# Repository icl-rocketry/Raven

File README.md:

# Project RAVEN

Solid-state particle detector for a rocket payload. Detects cosmic radiation
throughout flight and logs each hit with altitude, to build up counting
statistics post-flight.

Built in KiCad. Mixed-signal board: the detector board reads two independent
silicon-diode detector channels and logs events. 

## How it works 

A cosmic particle hits a reverse-biased photodiode and dumps a few femtocoulombs
of charge. A charge-sensitive amplifier turns that into a ~7 mV pulse, a
comparator checks it against a tunable threshold and the output signal is processed
by a seperate Pickle Rick board. Two diodes on two independent
channels double the sensitive area without doubling the noise.

## Repository layout

The KiCad project has five schematic sheets:
Using the ICLR Board Template

| Sheet | Contents |
|-------|----------|
| Root | status LEDs, connectors, test points |
| Power Board | Three isolated rails off a ~7.4V battery: +25V bias, +5V analogue, +3.3V digital |
| Detector Board | The signal chain: diodes, charge amps, comparators (2 channels) |

## specs

- **Enclosure:** Circa 90 x 90 x 100 mm (TBD), light-tight detector housing
- **Power:** ~1.5 W from a ~7.4V battery (cell TBC)
- **Detector:** 2x BPW34 photodiodes, biased at +50V
- **Front-end:** ADA4817-1 charge amp, TLV3201 comparator, per channel
- **MCU:** ESP32-S3

## Status

Work in progress. Schematic of the detector front-end is nearly
complete; layout, bring-up, and firmware still to come.

**Outstanding before layout:**
- Confirm comparator edge polarity on the bench (rising vs falling) before
  writing interrupt firmware
- Clear all ERC

## Firmware

Firmware is set up for PlatformIO. Clone the repo and open in PlatformIO to
build and flash.

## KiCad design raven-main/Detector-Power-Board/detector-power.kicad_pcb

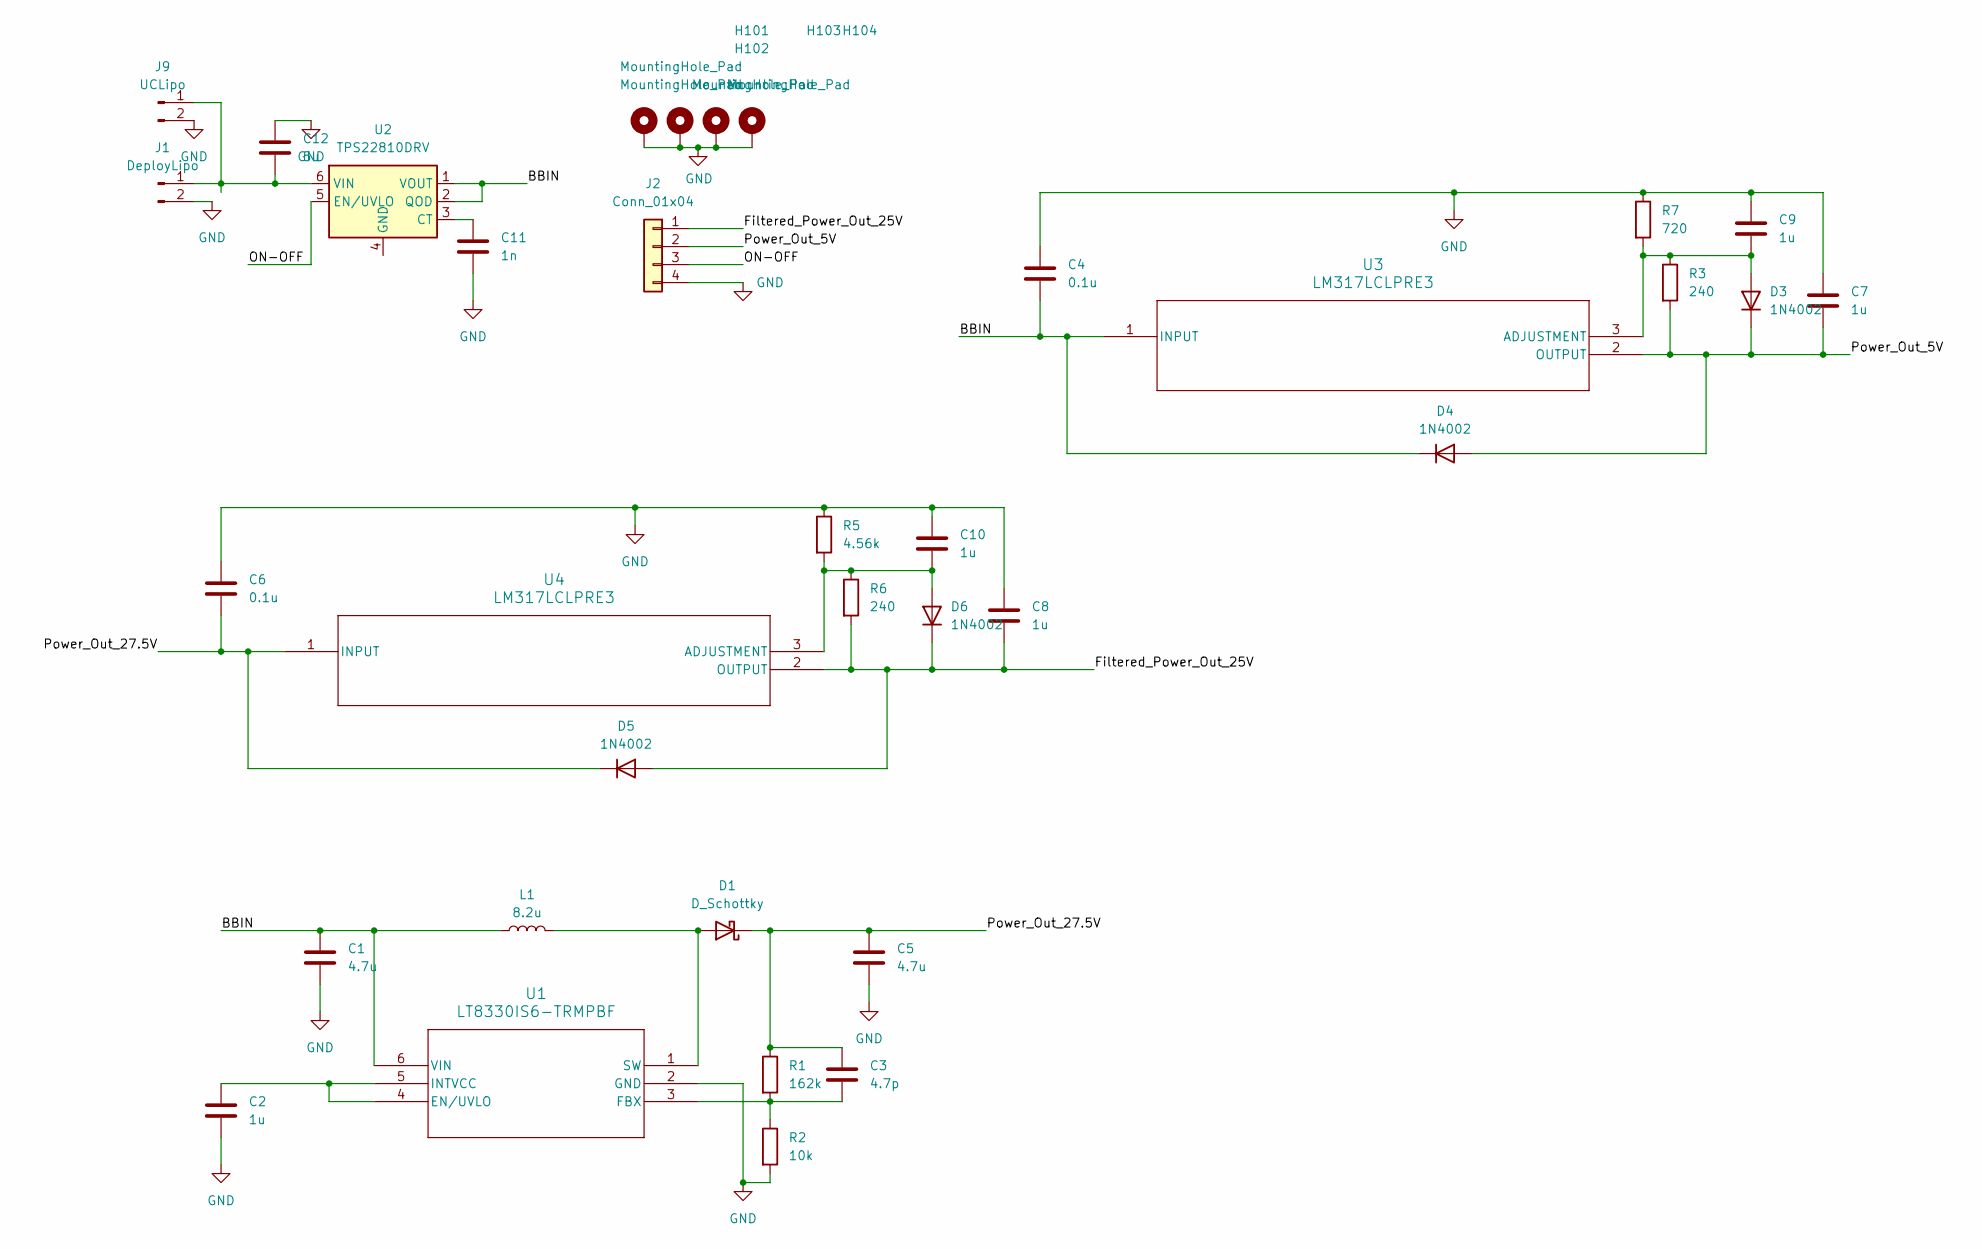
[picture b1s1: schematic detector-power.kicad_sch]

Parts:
C1, C5: 4.7u; C_0805_2012Metric
C2, C7, C8, C9, C10: 1u; C_0805_2012Metric
C3: 4.7p; C_0805_2012Metric
C4, C6: 0.1u; C_0805_2012Metric
C11: 1n; C_0805_2012Metric
C12: 5u; C_0805_2012Metric
D1: D_Schottky; SOD323F_NEX
D3, D4, D5, D6: 1N4002; D_DO-41_SOD81_P10.16mm_Horizontal
H101, H102, H103, H104: MountingHole_Pad; MountingHole_3.2mm_M3_DIN965_Pad
J1: DeployLipo; TerminalBlock_Phoenix_MKDS-3-2-5.08_1x02_P5.08mm_Horizontal
J2: Conn_01x04; PinHeader_1x04_P2.54mm_Vertical
J9: UCLipo; JST_PH_B2B-PH-K_1x02_P2.00mm_Vertical
L1: 8.2u; IND_8R0NC_SUM
R1: 162k; R_0402_1005Metric
R2: 10k; R_0402_1005Metric
R3, R6: 240; R_0402_1005Metric
R5: 4.56k; R_0402_1005Metric
R7: 720; R_0402_1005Metric
U1: LT8330IS6-TRMPBF; IC6_LT8330IS6-TRMPBF_ADI
U2: TPS22810DRV; WSON-6-1EP_2x2mm_P0.65mm_EP1x1.6mm
U3, U4: LM317LCLPRE3; TD03B_TEX

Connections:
/BBIN: C1.1, C4.2, D4.1 (K), L1.1, U1.6 (VIN), U2.1 (VOUT), U2.2 (QOD), U3.1 (INPUT)
/Filtered_Power_Out_25V: C8.2, D5.2 (A), D6.1 (K), J2.1, R6.2, U4.2 (OUTPUT)
/ON-OFF: J2.3, U2.5 (EN/UVLO)
/Power_Out_5V: C7.2, D3.1 (K), D4.2 (A), J2.2, R3.2, U3.2 (OUTPUT)
/Power_Out_27.5V: C3.1, C5.1, C6.2, D1.1 (K), D5.1 (K), R1.1, U4.1 (INPUT)
GND: C1.2, C2.2, C4.1, C5.2, C6.1, C7.1, C8.1, C9.1, C10.1, C11.2, C12.2, H101.1 (1_1), H102.1 (1_1), H103.1 (1_1), H104.1 (1_1), J1.2, J2.4, J9.2, R2.2, R5.1, R7.1, U1.2 (GND)
unnamed: D1.2 (A), L1.2, U1.1 (SW)
unnamed: C9.2, D3.2 (A), R3.1, R7.2, U3.3 (ADJUSTMENT)
unnamed: C10.2, D6.2 (A), R5.2, R6.1, U4.3 (ADJUSTMENT)
unnamed: C12.1, J1.1, J9.1, U2.6 (VIN)
unnamed: C2.1, U1.4 (EN/UVLO), U1.5 (INTVCC)
unnamed: C3.2, R1.2, R2.1, U1.3 (FBX)
unnamed: C11.1, U2.3 (CT)
unnamed: U2.4 (GND), U2.7 (GND)

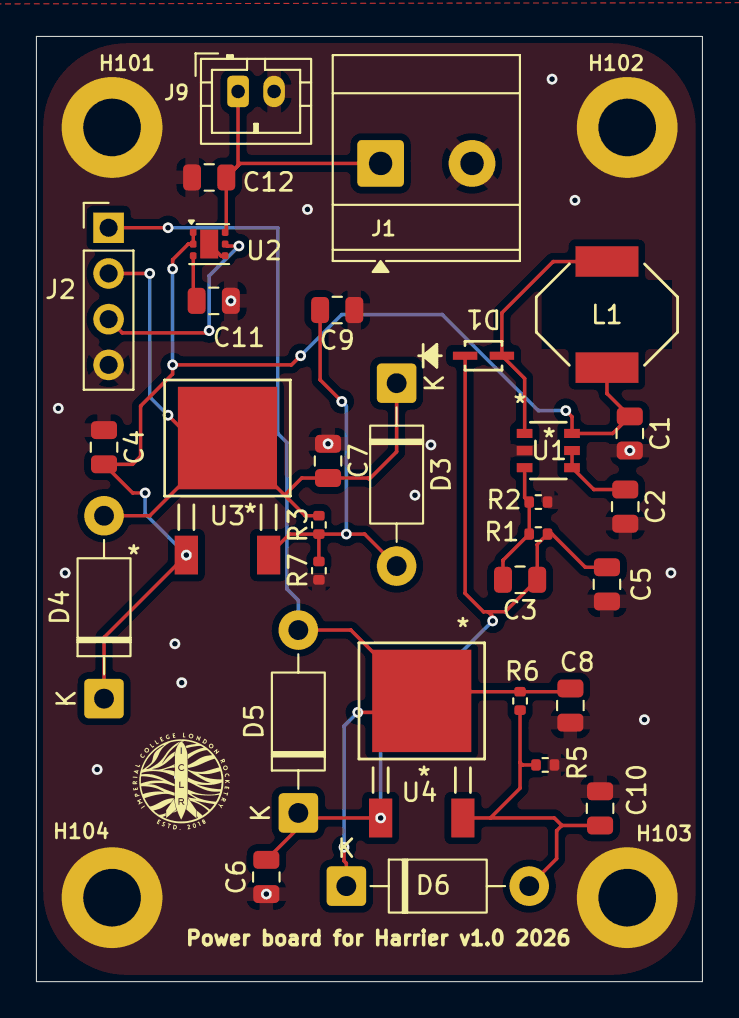
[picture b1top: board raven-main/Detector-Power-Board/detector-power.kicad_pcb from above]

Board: 2 copper layers, 37.0 x 52.5 mm, 35 parts (0 on the bottom side), 14 nets.

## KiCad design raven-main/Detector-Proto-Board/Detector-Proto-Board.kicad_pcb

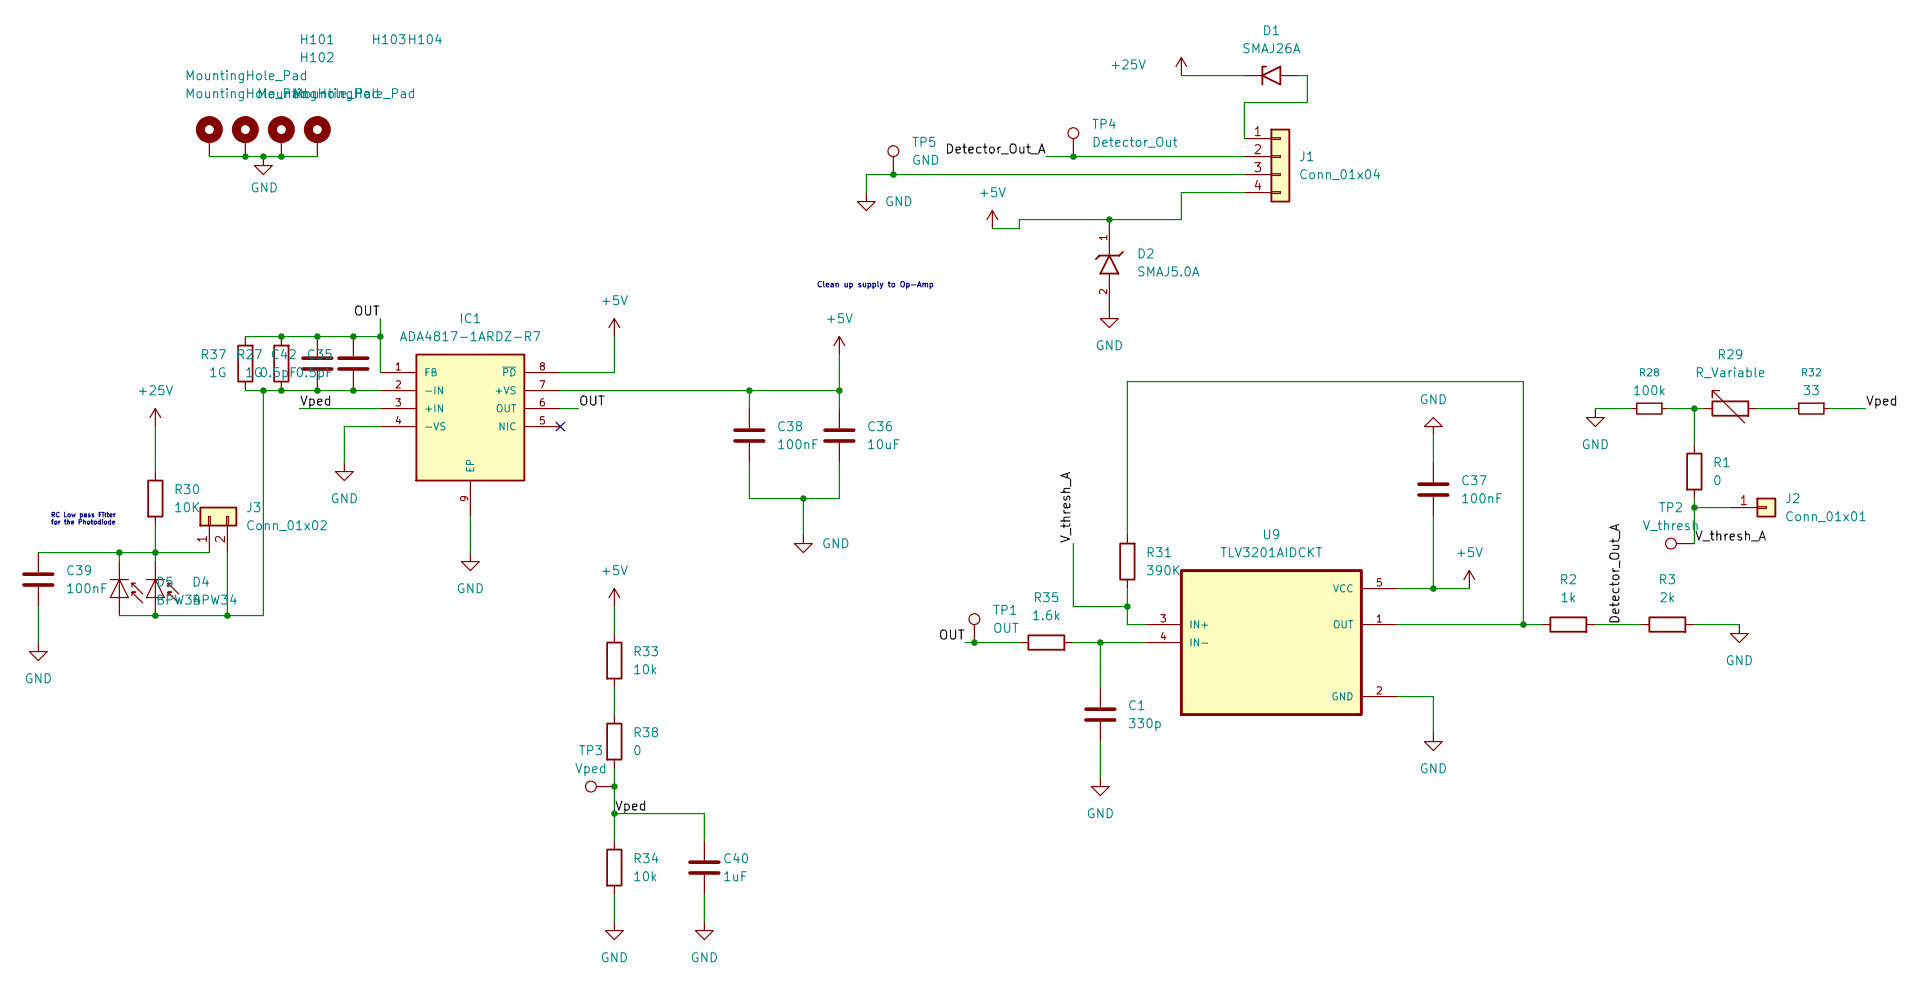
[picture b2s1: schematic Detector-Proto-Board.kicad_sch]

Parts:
C1: 330p; C_0402_1005Metric
C35, C42: 0.5pF; C_0402_1005Metric
C36: 10uF; C_0402_1005Metric
C37, C38, C39: 100nF; C_0402_1005Metric
C40: 1uF; C_0402_1005Metric
D1: SMAJ26A; D_SMA
D2: SMAJ5.0A; D_SMA; MOUSER_PART_NUMBER 576-SMAJ5.0A
D4, D5: BPW34; Osram_DIL2_4.3x4.65mm_P5.08mm
H101, H102, H103, H104: MountingHole_Pad; MountingHole_3.2mm_M3_DIN965_Pad
IC1: ADA4817-1ARDZ-R7; SOIC127P600X175-9N; Mouser_Part_Number 584-ADA4817-1ARDZ-R7
J1: Conn_01x04; PinHeader_1x04_P2.54mm_Vertical
J2: Conn_01x01; PinHeader_1x01_P2.54mm_Vertical
J3: Conn_01x02; PinHeader_1x02_P2.54mm_Vertical
R1, R38: 0; R_0402_1005Metric
R2: 1k; R_0402_1005Metric
R3: 2k; R_0402_1005Metric
R27, R37: 1G; R_0402_1005Metric
R28: 100k; R_0402_1005Metric
R29: R_Variable; SOT_502E
R30: 10K; R_0402_1005Metric
R31: 390K; R_0402_1005Metric
R32: 33; R_0402_1005Metric
R33, R34: 10k; R_0402_1005Metric
R35: 1.6k; R_0402_1005Metric
TP1: OUT; TestPoint_Pad_D2.5mm
TP2: V_thresh; TestPoint_Pad_D2.5mm
TP3: Vped; TestPoint_Pad_D2.5mm
TP4: Detector_Out; TestPoint_Pad_D2.5mm
TP5: GND; TestPoint_Pad_D2.5mm
U9: TLV3201AIDCKT; SOT65P210X110-5N

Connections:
+5V: C36.1, C37.2, C38.2, D2.1, IC1.7 (+VS), IC1.8 (~PD), J1.4, R33.1, U9.5 (VCC)
+25V: D1.1 (A1), R30.1
/Detector_Out_A: J1.2, R2.2, R3.1, TP4.1 (1_1)
/OUT: C35.2, C42.2, IC1.1 (FB), IC1.6 (OUT), R27.2, R35.1, R37.2, TP1.1 (1_1)
/V_thresh_A: J2.1 (Pin_1_1), R1.2, R31.1, TP2.1 (1_1), U9.3 (IN+)
/Vped: C40.1, IC1.3 (+IN), R32.1, R34.1, R38.2, TP3.1 (1_1)
GND: C1.2, C36.2, C37.1, C38.1, C39.2, C40.2, D2.2, H101.1 (1_1), H102.1 (1_1), H103.1 (1_1), H104.1 (1_1), IC1.4 (-VS), IC1.9 (EP), J1.3, R3.2, R28.2, R34.2, TP5.1 (1_1), U9.2 (GND)
unnamed: D1.2 (A2), J1.1
unnamed: C35.1, C42.1, D4.2 (A), D5.2 (A), IC1.2 (-IN), J3.2, R27.1, R37.1
unnamed: C39.1, D4.1 (K), D5.1 (K), J3.1, R30.2
unnamed: R1.1, R28.1, R29.1
unnamed: R29.2, R32.2
unnamed: R33.2, R38.1
unnamed: C1.1, R35.2, U9.4 (IN-)
unnamed: R2.1, R31.2, U9.1 (OUT)

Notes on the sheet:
Clean up supply to Op-Amp
RC Low pass Filter for the Photodiode

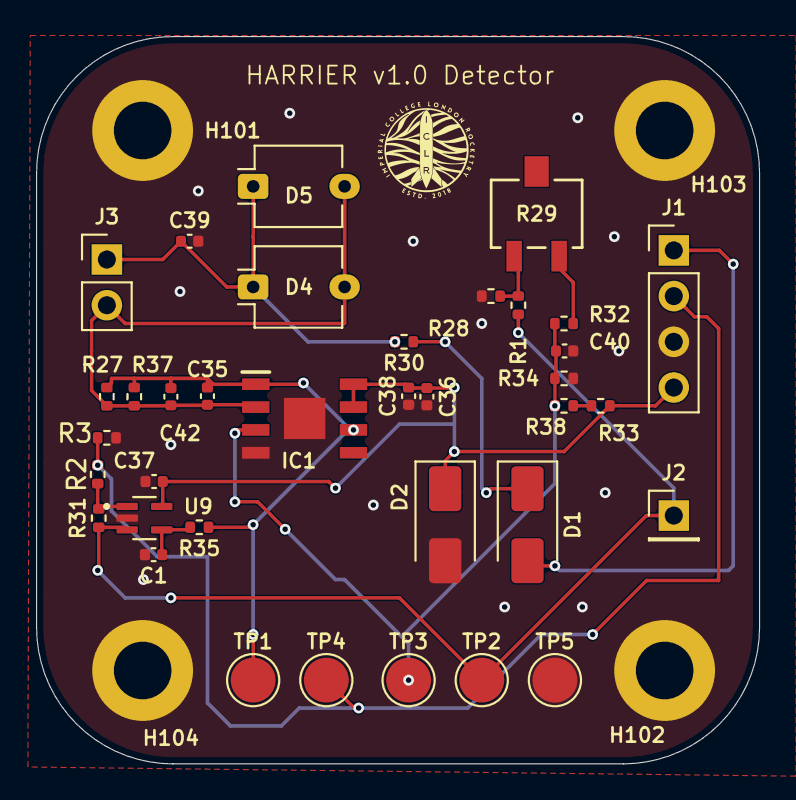
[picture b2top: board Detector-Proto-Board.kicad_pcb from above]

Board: 2 copper layers, 40.2 x 40.4 mm, 40 parts (0 on the bottom side), 15 nets.

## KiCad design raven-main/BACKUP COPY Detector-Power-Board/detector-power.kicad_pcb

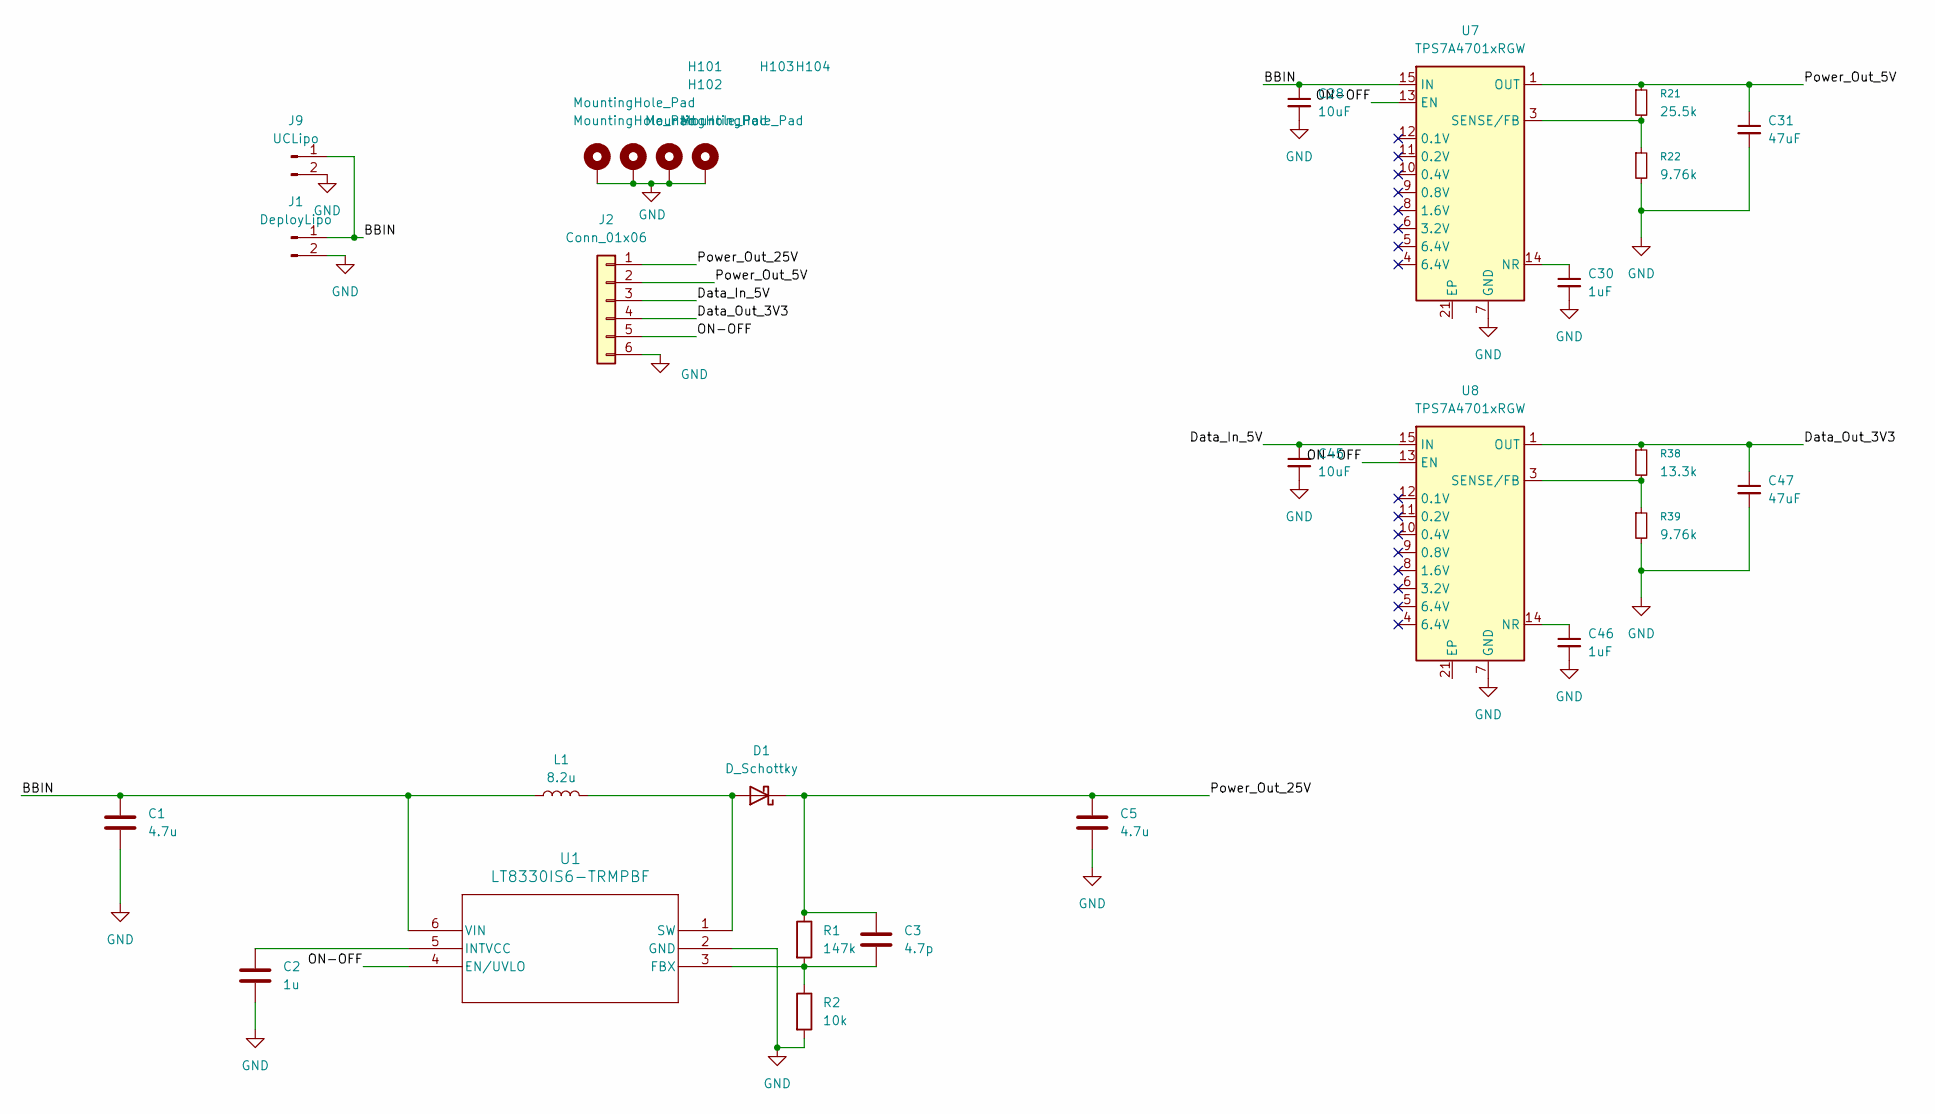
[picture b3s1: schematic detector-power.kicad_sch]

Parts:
C1, C5: 4.7u; C_0805_2012Metric
C2: 1u; C_0805_2012Metric
C3: 4.7p; C_0805_2012Metric
C28, C45: 10uF; C_0805_2012Metric
C30, C46: 1uF; C_0805_2012Metric
C31, C47: 47uF; C_0805_2012Metric
D1: D_Schottky; SOD323F_NEX
H101, H102, H103, H104: MountingHole_Pad; MountingHole_3.2mm_M3_DIN965_Pad
J1: DeployLipo; TerminalBlock_Phoenix_MKDS-3-2-5.08_1x02_P5.08mm_Horizontal
J2: Conn_01x06; TerminalBlock_4Ucon_1x06_P3.50mm_Horizontal
J9: UCLipo; JST_PH_B2B-PH-K_1x02_P2.00mm_Vertical
L1: 8.2u; IND_8R0NC_SUM
R1: 147k; R_0402_1005Metric
R2: 10k; R_0402_1005Metric
R21: 25.5k; R_0402_1005Metric
R22, R39: 9.76k; R_0402_1005Metric
R38: 13.3k; R_0402_1005Metric
U1: LT8330IS6-TRMPBF; IC6_LT8330IS6-TRMPBF_ADI
U7, U8: TPS7A4701xRGW; Texas_RGW0020A_VQFN-20-1EP_5x5mm_P0.65mm_EP3.15x3.15mm_Ther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

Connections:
/BBIN: C1.1, C28.1, J1.1, J9.1, L1.1, U1.6 (VIN), U7.15 (IN), U7.16 (IN)
/Data_In_5V: C45.1, J2.3, U8.15 (IN), U8.16 (IN)
/Data_Out_3V3: C47.1, J2.4, R38.1, U8.1 (OUT), U8.20 (OUT)
/ON-OFF: J2.5, U1.4 (EN/UVLO), U7.13 (EN), U8.13 (EN)
/Power_Out_5V: C31.1, J2.2, R21.1, U7.1 (OUT), U7.20 (OUT)
/Power_Out_25V: C3.1, C5.1, D1.1 (K), J2.1, R1.1
GND: C1.2, C2.2, C5.2, C28.2, C30.2, C31.2, C45.2, C46.2, C47.2, H101.1 (1_1), H102.1 (1_1), H103.1 (1_1), H104.1 (1_1), J1.2, J2.6, J9.2, R2.2, R22.2, R39.2, U1.2 (GND), U7.7 (GND), U8.7 (GND)
unnamed: D1.2 (A), L1.2, U1.1 (SW)
unnamed: C3.2, R1.2, R2.1, U1.3 (FBX)
unnamed: C2.1, U1.5 (INTVCC)
unnamed: C30.1, U7.14 (NR)
unnamed: R21.2, R22.1, U7.3 (SENSE/FB)
unnamed: C46.1, U8.14 (NR)
unnamed: R38.2, R39.1, U8.3 (SENSE/FB)

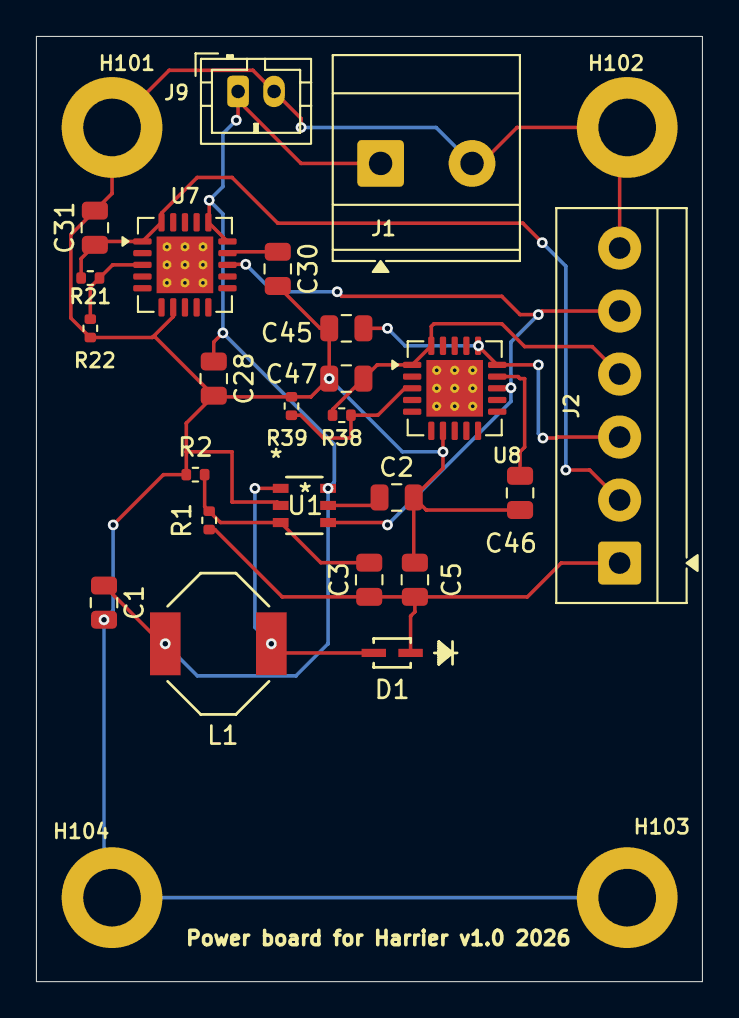
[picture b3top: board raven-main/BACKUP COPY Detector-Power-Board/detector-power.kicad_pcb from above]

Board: 2 copper layers, 37.0 x 52.5 mm, 28 parts (0 on the bottom side), 14 nets.

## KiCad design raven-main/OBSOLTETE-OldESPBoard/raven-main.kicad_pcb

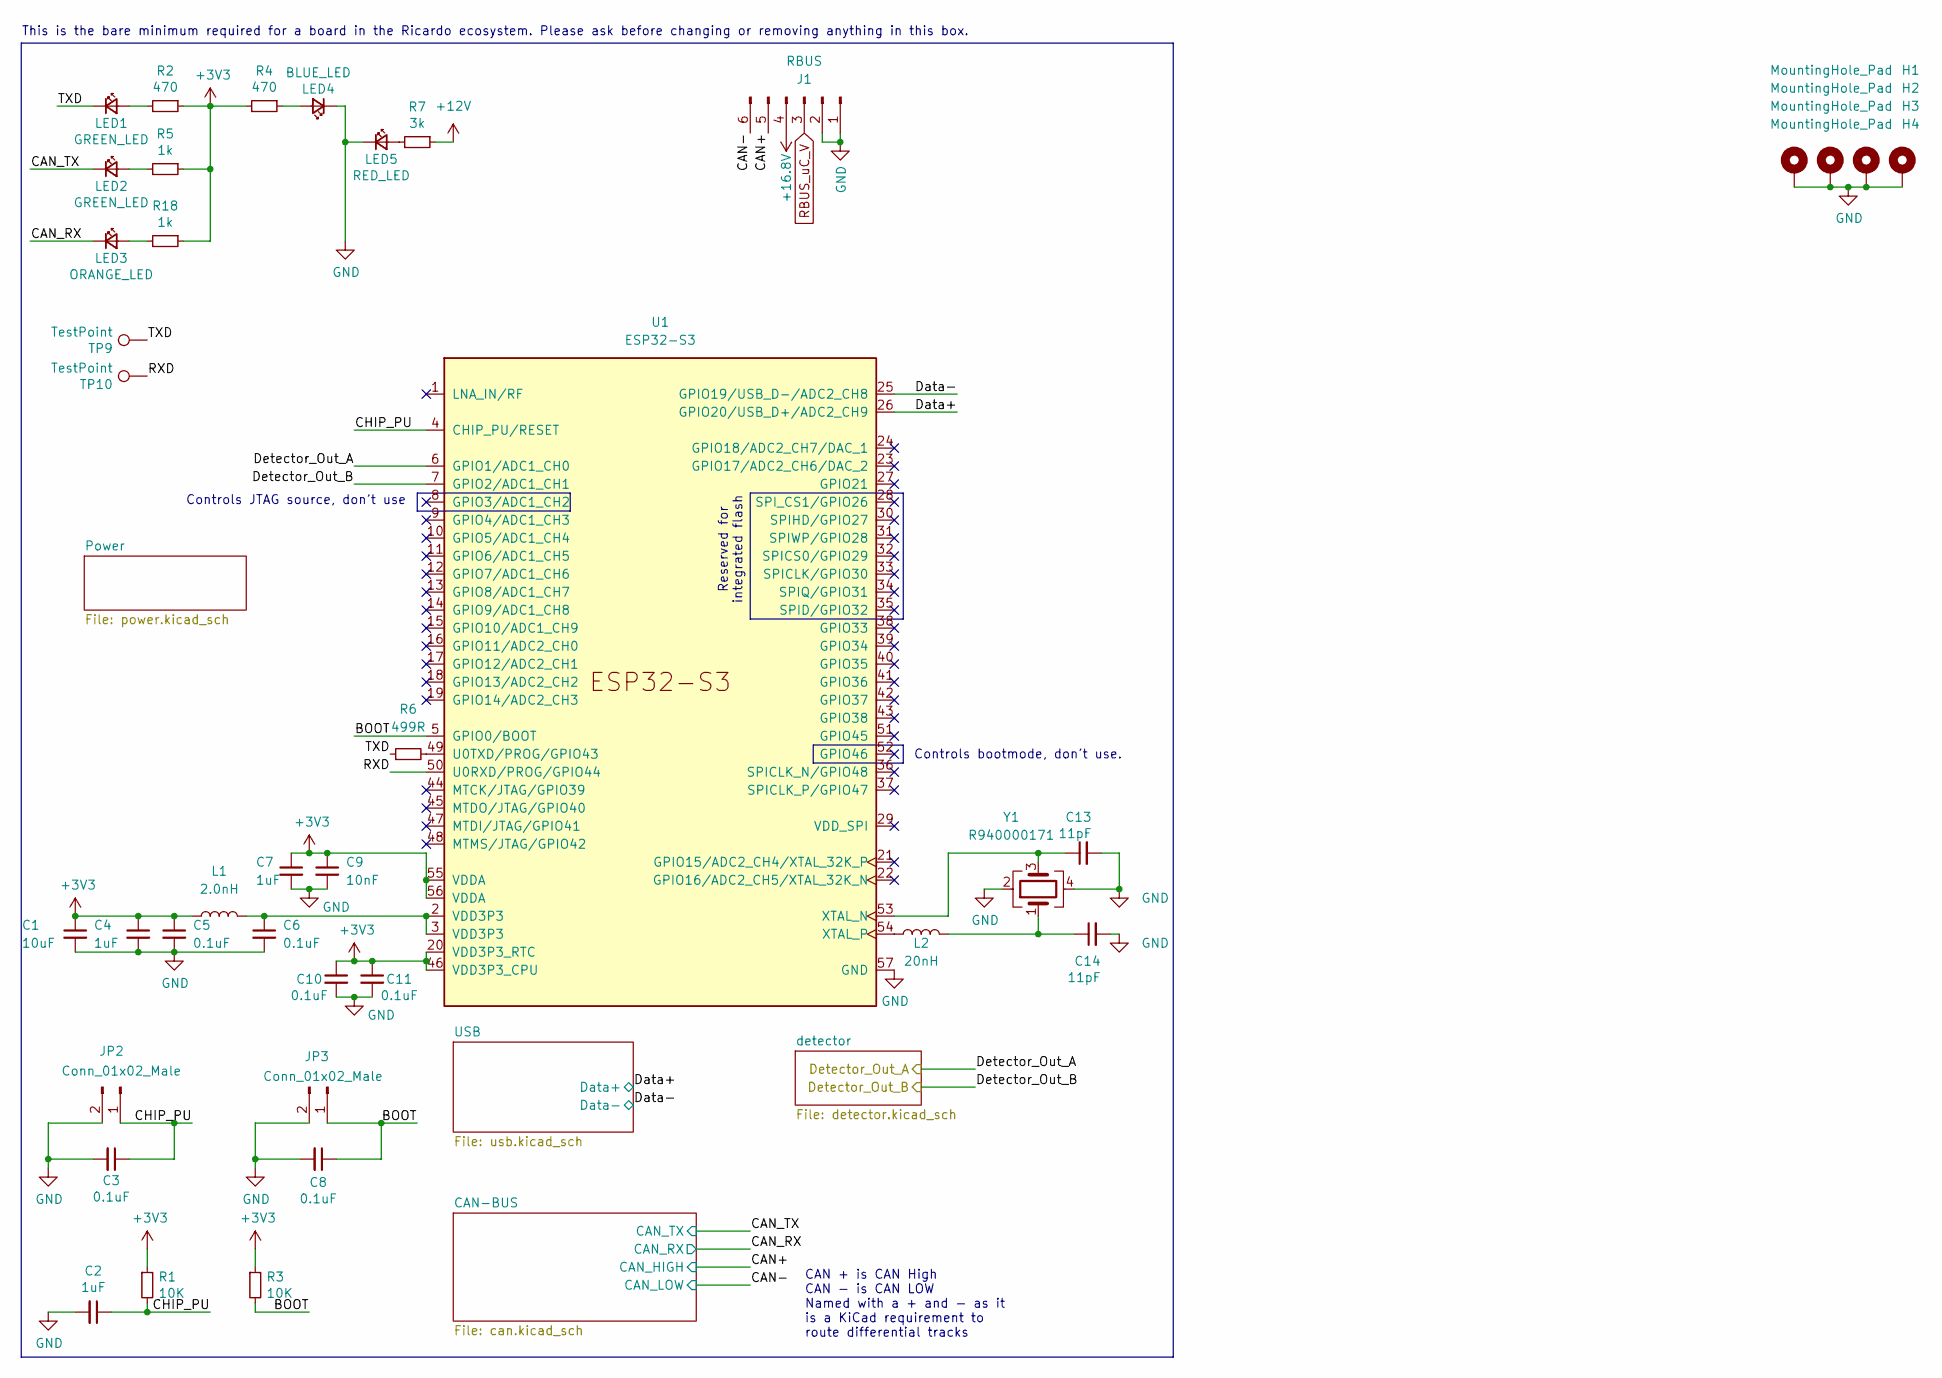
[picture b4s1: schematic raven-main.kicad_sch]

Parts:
C1: 10uF; C_0402_1005Metric
C2, C4, C7: 1uF; C_0402_1005Metric
C3, C5, C6, C8, C10, C11: 0.1uF; C_0402_1005Metric
C9: 10nF; C_0402_1005Metric
C13, C14: 11pF; C_0402_1005Metric
H1, H2, H3, H4: MountingHole_Pad; MountingHole_3.2mm_M3_DIN965_Pad
J1: RBUS; Molex_Mini-Fit_Jr_5569-06A2_2x03_P4.20mm_Horizontal
JP2, JP3: Conn_01x02_Male; PinHeader_1x02_P2.54mm_Vertical
L1: 2.0nH; L_0402_1005Metric
L2: 20nH; L_0402_1005Metric
LED1, LED2: GREEN_LED; LED_0402_1005Metric
LED3: ORANGE_LED; LED_0402_1005Metric
LED4: BLUE_LED; LED_0402_1005Metric
LED5: RED_LED; LED_0402_1005Metric
R1, R3: 10K; R_0402_1005Metric
R2, R4: 470; R_0402_1005Metric
R5, R18: 1k; R_0402_1005Metric
R6: 499R; R_0402_1005Metric
R7: 3k; R_0402_1005Metric
TP9, TP10: TestPoint; TestPoint_Pad_D1.0mm
U1: ESP32-S3; QFN40P700X700X90-57N
Y1: R940000171; Crystal_SMD_2016-4Pin_2.0x1.6mm

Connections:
+3V3: C1.1, C4.1, C5.1, C7.1, C9.1, C10.1, C11.1, L1.1, R1.1, R2.1, R3.1, R4.2, R5.1, R18.1, U1.20 (VDD3P3_RTC), U1.46 (VDD3P3_CPU), U1.55 (VDDA), U1.56 (VDDA); also elsewhere on the board
+12V: R7.1
+16.8V: J1.4
+50V: C1.2, C2.2, C3.2, C4.2, C5.2, C6.2, C7.2, C8.2, C9.2, C10.2, C11.2, C13.2, C14.2, H1.1 (1_1), H2.1 (1_1), H3.1 (1_1), H4.1 (1_1), J1.1, J1.2, JP2.2, JP3.2, LED4.1 (K), LED5.1 (K), U1.57 (GND), Y1.2, Y1.4; also elsewhere on the board
/BOOT: C8.1, JP3.1, R3.2, U1.5 (GPIO0/BOOT)
/CAN+: J1.5; also elsewhere on the board
/CAN-: J1.6; also elsewhere on the board
/CAN_RX: LED3.1 (K); also elsewhere on the board
/CAN_TX: LED2.1 (K); also elsewhere on the board
/CHIP_PU: C2.1, C3.1, JP2.1, R1.2, U1.4 (CHIP_PU/RESET)
/Data+: U1.26 (GPIO20/USB_D+/ADC2_CH9); also elsewhere on the board
/Data-: U1.25 (GPIO19/USB_D-/ADC2_CH8); also elsewhere on the board
/Detector_Out_A: U1.6 (GPIO1/ADC1_CH0)
/Detector_Out_B: U1.7 (GPIO2/ADC1_CH1)
/RXD: TP10.1 (1_1), U1.50 (U0RXD/PROG/GPIO44)
/TXD: LED1.1 (K), R6.1, TP9.1 (1_1)
unnamed: C6.1, L1.2, U1.2 (VDD3P3), U1.3 (VDD3P3)
unnamed: C14.1, L2.2, Y1.1
unnamed: LED1.2 (A), R2.2
unnamed: LED2.2 (A), R5.2
unnamed: LED3.2 (A), R18.2
unnamed: LED4.2 (A), R4.1
unnamed: LED5.2 (A), R7.2
unnamed: R6.2, U1.49 (U0TXD/PROG/GPIO43)
unnamed: C13.1, U1.53 (XTAL_N), Y1.3
unnamed: L2.1, U1.54 (XTAL_P)
RBUS_uC_V: J1.3; also elsewhere on the board

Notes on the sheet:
Controls bootmode, don't use.
This is the bare minimum required for a board in the Ricardo ecosystem. Please ask before changing or removing anything in this box.
CAN + is CAN High CAN - is CAN LOW Named with a + and - as it is a KiCad requirement to route differential tracks
Controls JTAG source, don't use
Reserved for integrated flash

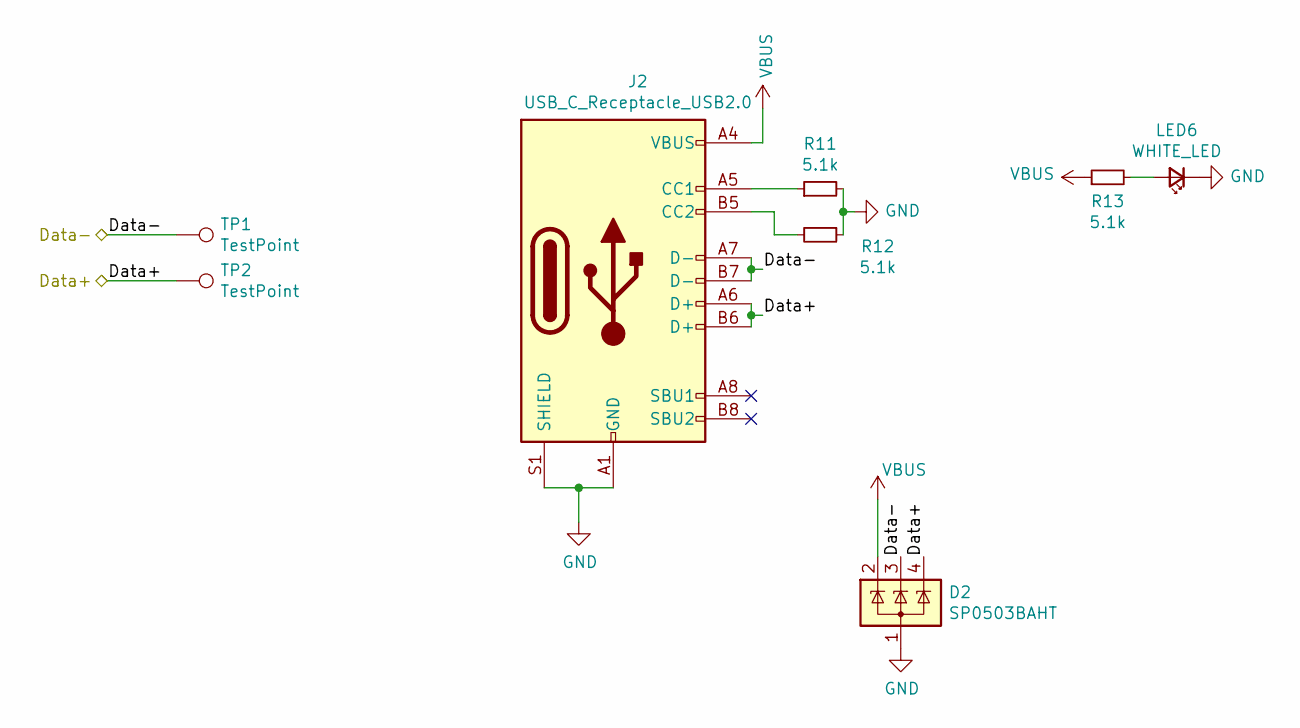
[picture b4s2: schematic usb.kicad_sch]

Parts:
D2: SP0503BAHT; SOT-143
J2: USB_C_Receptacle_USB2.0; USB_C_Receptacle_Palconn_UTC16-G
LED6: WHITE_LED; LED_0402_1005Metric
R11, R12, R13: 5.1k; R_0402_1005Metric
TP1, TP2: TestPoint; TestPoint_Pad_D1.0mm

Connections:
+50V: D2.1 (A), J2.A1 (GND), J2.A12 (GND), J2.B1 (GND), J2.B12 (GND), J2.S1 (SHIELD), LED6.1 (K), R11.2, R12.1; also elsewhere on the board
/Data+: D2.4 (K), J2.A6 (D+), J2.B6 (D+), TP2.1 (1_1); also elsewhere on the board
/Data-: D2.3 (K), J2.A7 (D-), J2.B7 (D-), TP1.1 (1_1); also elsewhere on the board
unnamed: J2.A5 (CC1), R11.1
unnamed: J2.B5 (CC2), R12.2
unnamed: LED6.2 (A), R13.2
VBUS: D2.2 (K), J2.A4 (VBUS), J2.A9 (VBUS), J2.B4 (VBUS), J2.B9 (VBUS), R13.1; also elsewhere on the board

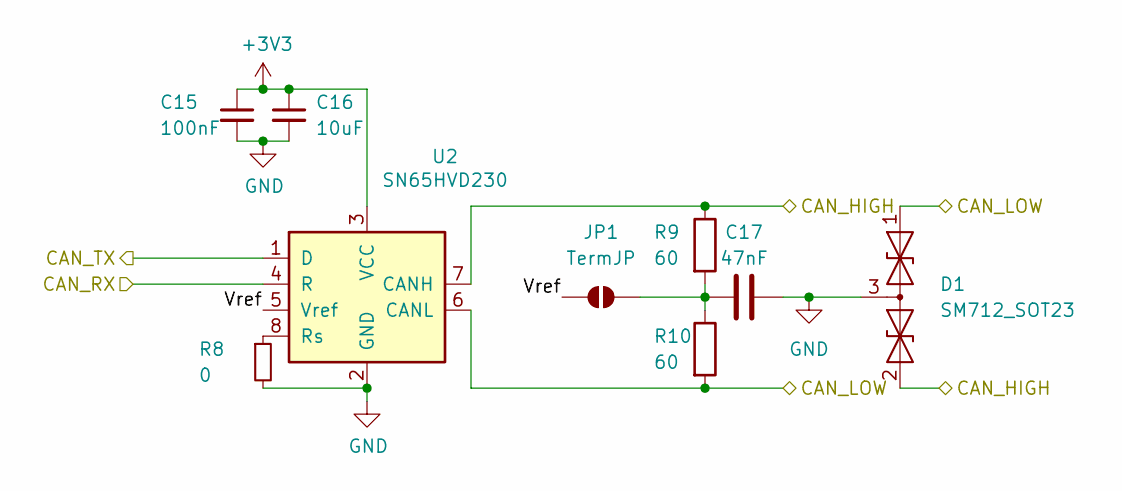
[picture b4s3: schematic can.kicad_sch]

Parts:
C15: 100nF; C_0402_1005Metric
C16: 10uF; C_0402_1005Metric
C17: 47nF; C_0402_1005Metric
D1: SM712_SOT23; SOT-23
JP1: TermJP; SmallerSolderJP
R8: 0; R_0603_1608Metric
R9, R10: 60; R_0603_1608Metric
U2: SN65HVD230; SOIC-8_3.9x4.9mm_P1.27mm

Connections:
+3V3: C15.1, C16.1, U2.3 (VCC); also elsewhere on the board
+50V: C15.2, C16.2, C17.2, D1.3 (common), R8.2, U2.2 (GND); also elsewhere on the board
/CAN+: D1.2 (A2), R9.1, U2.7 (CANH); also elsewhere on the board
/CAN-: D1.1 (A1), R10.2, U2.6 (CANL); also elsewhere on the board
/CAN-BUS/Vref: JP1.1 (A), U2.5 (Vref)
/CAN_RX: U2.4 (R); also elsewhere on the board
/CAN_TX: U2.1 (D); also elsewhere on the board
unnamed: C17.1, JP1.2 (B), R9.2, R10.1
unnamed: R8.1, U2.8 (Rs)
